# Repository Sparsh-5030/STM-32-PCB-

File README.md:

# STM-32-PCB-
This is a simple pcb design of STM32F405GT controller using KiCad

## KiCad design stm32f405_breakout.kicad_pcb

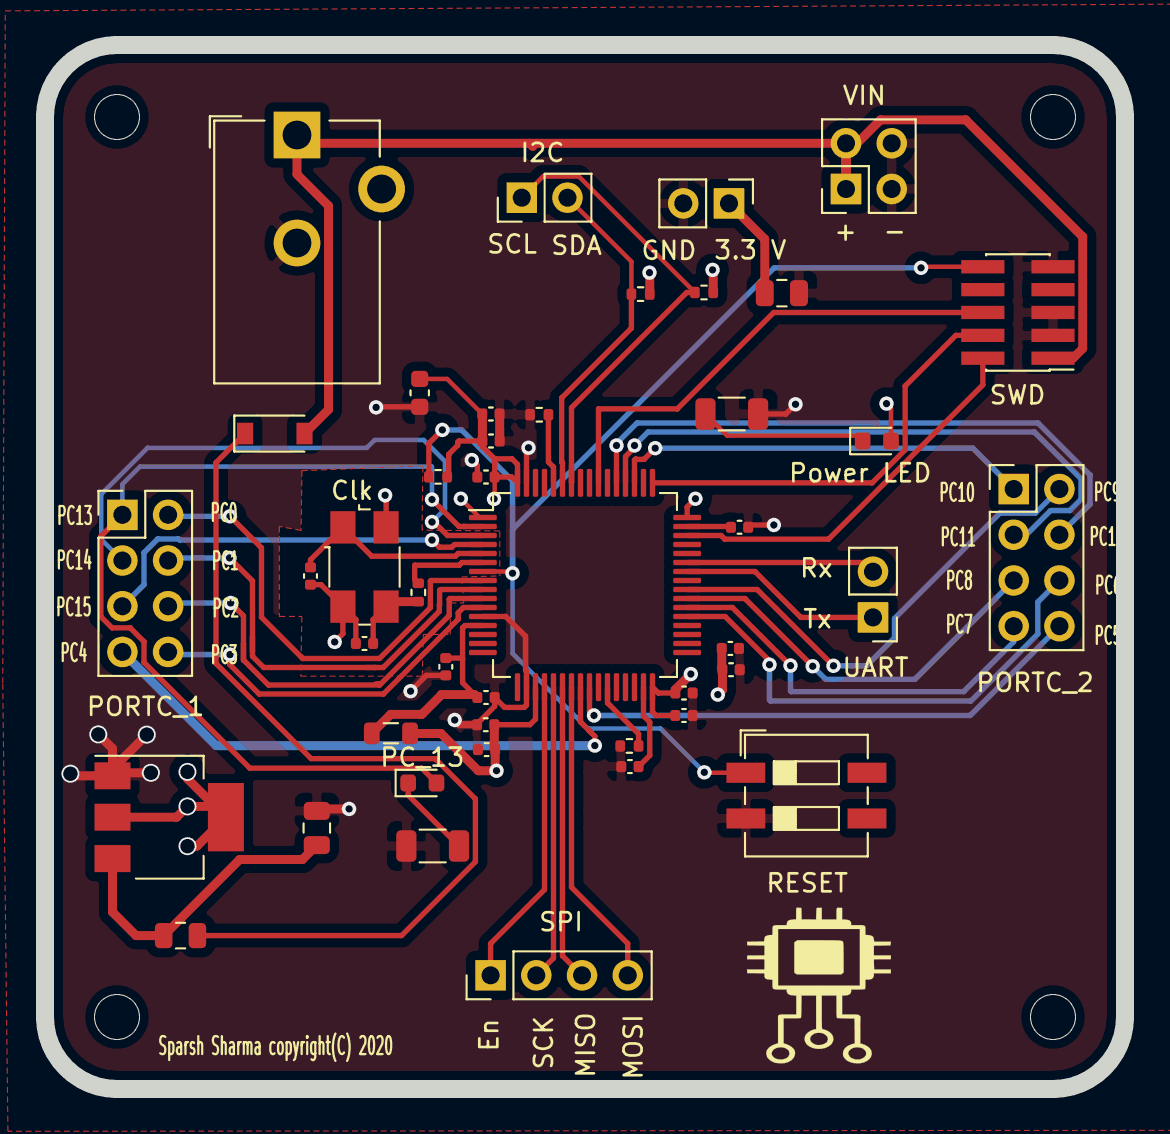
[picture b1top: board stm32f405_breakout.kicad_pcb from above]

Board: 4 copper layers, 60.0 x 58.0 mm, 48 parts (0 on the bottom side), 43 nets.

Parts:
3.3 V: Conn_01x02; PinHeader_1x02_P2.54mm_Vertical
C1: 10uF; C_0603_1608Metric
C2, C4, C6, C7, C8, C9, C10, C11, C12, C16: 100nF; C_0402_1005Metric
C3, C5: 2.2uF; C_0402_1005Metric
C13, C14: 12pF; C_0402_1005Metric
C15, C18: 10uF; C_0805_2012Metric
C17: 10nF; C_0402_1005Metric
D1: D_Schottky; D_SOD-123
D2: LED; LED_0603_1608Metric
F1: Fuse; Fuse_0805_2012Metric
FB1: Ferrite_Bead; L_0805_2012Metric
H1, H2, H3, H4: MountingHole; MountingHole_2.5mm
I2C: Conn_01x02; PinHeader_1x02_P2.54mm_Vertical
J1: Conn_02x05_Odd_Even; PinHeader_2x05_P1.27mm_Vertical_SMD
J7: Barrel_Jack; BarrelJack_CUI_PJ-102AH_Horizontal
PC_13: LED; LED_0603_1608Metric
PORTC_1, PORTC_2: Conn_02x04_Odd_Even; PinHeader_2x04_P2.54mm_Vertical
R1: 220; R_0402_1005Metric
R2, R3: 2k; R_0402_1005Metric
R4, R5, R6: 10K; R_0402_1005Metric
R7, R8: 2.2k; R_1206_3216Metric
RESET: SW_Push; SW_DIP_SPSTx02_Slide_6.7x6.64mm_W6.73mm_P2.54mm_LowProfile_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
SPI: Conn_01x04; PinHeader_1x04_P2.54mm_Vertical
U1: STM32F405RGTx; LQFP-64_10x10mm_P0.5mm
U2: AMS1117-3.3; SOT-223-3_TabPin2
UART: Conn_01x02; PinHeader_1x02_P2.54mm_Vertical
VIN: Conn_02x02_Odd_Even; PinHeader_2x02_P2.54mm_Vertical
Y1: Crystal_GND24; Crystal_SMD_0603-4Pin_6.0x3.5mm

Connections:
+3.3VA: C16.1, C17.1, FB1.1, U1.13
+3V3: 3.3 V.1, C1.1, C2.1, C4.1, C6.1, C7.1, C8.1, C9.1, C10.1, C11.1, C12.1, C18.1, D2.2, FB1.2, R2.1, R3.1, R4.1, U1.1, U1.19, U1.32, U1.48, U1.64, U2.2
BOOT0: R5.2, U1.60
BOOT1: R6.2, U1.27
GND: 3.3 V.2, C1.2, C2.2, C3.2, C4.2, C5.2, C6.2, C7.2, C8.2, C9.2, C10.2, C11.2, C12.2, C13.2, C14.2, C15.2, C16.2, C17.2, C18.2, J1.3, J1.5, J1.9, J7.2, R5.1, R6.1, R7.2, R8.2, RESET.2, U1.12, U1.18, U1.63, U2.1, VIN.3, VIN.4, Y1.2, Y1.4
I2C1_SCL: I2C.1, R2.2, U1.58
I2C1_SDA: I2C.2, R3.2, U1.59
NRESET: J1.10, R4.2, RESET.1, U1.7
unnamed: C3.1, U1.31
unnamed: C5.1, U1.47
unnamed: C14.1, R1.2, Y1.3
unnamed: C15.1, F1.1, U2.3
unnamed: D1.1, F1.2
unnamed: D2.1, R7.1
unnamed: PC_13.1, R8.1
PC0: PORTC_1.2, U1.8
PC1: PORTC_1.4, U1.9
PC2: PORTC_1.6, U1.10
PC3: PORTC_1.8, U1.11
PC4: PORTC_1.7, U1.24
PC5: PORTC_2.8, U1.25
PC6: PORTC_2.6, U1.37
PC7: PORTC_2.7, U1.38
PC8: PORTC_2.5, U1.39
PC9: PORTC_2.2, U1.40
PC10: PORTC_2.1, U1.51
PC11: PORTC_2.3, U1.52
PC12: PORTC_2.4, U1.53
PC13: PC_13.2, PORTC_1.1, U1.2
PC14: PORTC_1.3, U1.3
PC15: PORTC_1.5, U1.4
RCC_OSC_IN: C13.1, U1.5, Y1.1
RCC_OSC_OUT: R1.1, U1.6
SPI1_EN: SPI.1, U1.20
SPI1_MISO: SPI.3, U1.22
SPI1_MOSI: SPI.4, U1.23
SPI1_SCK: SPI.2, U1.21
SWCLK: J1.4, U1.49
SWDIO: J1.2, U1.46
SWO: J1.6, U1.55
USART1_RX: U1.43, UART.2
USART1_TX: U1.42, UART.1
VCC: D1.2, J1.1, J7.1, VIN.1, VIN.2

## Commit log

2020-11-24 Create README.md
    Readme Commit

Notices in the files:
stm32f405_breakout.kicad_pcb:
Sparsh Sharma copyright(C) 2020
